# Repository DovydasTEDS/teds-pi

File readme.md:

# teds pi
  
RK3588S based SBC with LPDDR4X RAM in a hopefully pi-shaped shape (what)

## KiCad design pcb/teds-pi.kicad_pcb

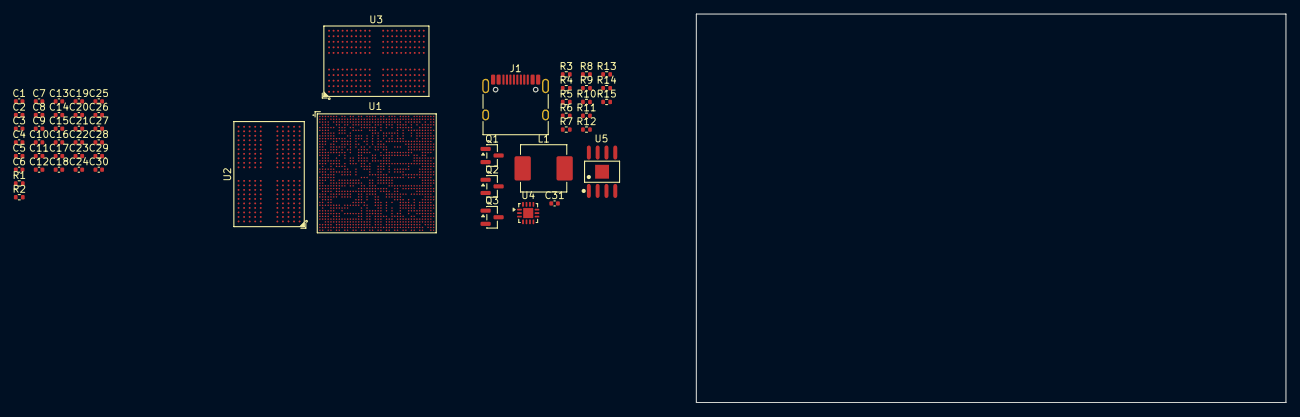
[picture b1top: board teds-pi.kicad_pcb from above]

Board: 6 copper layers, 85.0 x 56.0 mm, 56 parts (0 on the bottom side), 149 nets, no tracks yet.

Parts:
C1, C19: 2.2uF; C_0402_1005Metric
C2, C6, C8, C13, C14, C24, C25, C26, C27, C28, C29, C30, C31: 0.1uF; C_0402_1005Metric
C3, C7, C9, C10, C15, C16, C17, C18: 4.7uF; C_0402_1005Metric
C4, C5, C11, C12, C20, C21, C22, C23: 1uF; C_0402_1005Metric
J1: USB_C_Receptacle_USB2.0_16P; USB_C_Receptacle_HRO_TYPE-C-31-M-12
L1: 4.7uH; L_Changjiang_FXL0630
Q1, Q2: AO3401A; SOT-23
Q3: 2N7002; SOT-23
R1, R2: 240R; R_0402_1005Metric
R3, R4, R5, R6: 49.9R; R_0402_1005Metric
R7, R8: 4k7; R_0402_1005Metric
R9: 10R; R_0402_1005Metric
R10: 10K; R_0402_1005Metric
R11, R13: 100k; R_0402_1005Metric
R12: 10k; R_0402_1005Metric
R14: 44.2k; R_0402_1005Metric
R15: 6.04k; R_0402_1005Metric
U1: BGA-1253_L17.0-W17.0-P0.40-TL
U2, U3: FBGA-200_L15.0-W10.0-BL_K4F6E3S4HM
U4: FUSB302BMPX; WQFN-14-1EP_2.5x2.5mm_P0.5mm_EP1.45x1.45mm
U5: SOIC-8_L5.0-W4.0-P1.27-LS6.0-BL-EP2.0

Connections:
+0V6_DDR: C9.1, C10.1, C11.1, C12.1, C13.1, C14.1, C16.1, C18.1, C21.1, C23.1, C26.1, C28.1, C29.1, C30.1, U1.H14 (DDR_CH1_VDDQ_1), U1.H15 (DDR_CH1_VDDQ_2), U1.H16 (DDR_CH1_VDDQ_3), U1.H18 (DDR_CH1_VDDQ_4), U1.H20 (DDR_CH1_VDDQ_5), U1.K9 (DDR_CH0_VDDQ_CK_1), U1.L9 (DDR_CH0_VDDQ_CK_2), U1.M6 (DDR_CH0_VDDQ_CKE_1), U1.M7 (DDR_CH0_VDDQ_CKE_2), U1.P10 (DDR_CH0_VDDQ_1), U1.R10 (DDR_CH0_VDDQ_2), U1.T10 (DDR_CH0_VDDQ_3), U1.V10 (DDR_CH0_VDDQ_4), U1.W10 (DDR_CH0_VDDQ_5), U1.Y10 (DDR_CH0_VDDQ_6), U2.AA3 (VDDQ), U2.AA5 (VDDQ), U2.AA8 (VDDQ), U2.AA10 (VDDQ), U2.B3 (VDDQ), U2.B5 (VDDQ), U2.B8 (VDDQ), U2.B10 (VDDQ), U2.D1 (VDDQ), U2.D5 (VDDQ), U2.D8 (VDDQ), U2.D12 (VDDQ), U2.F3 (VDDQ), U2.F10 (VDDQ), U2.U3 (VDDQ), U2.U10 (VDDQ), U2.W1 (VDDQ), U2.W5 (VDDQ), U2.W8 (VDDQ), U2.W12 (VDDQ), U3.AA3 (VDDQ), U3.AA5 (VDDQ), U3.AA8 (VDDQ), U3.AA10 (VDDQ), U3.B3 (VDDQ), U3.B5 (VDDQ), U3.B8 (VDDQ), U3.B10 (VDDQ), U3.D1 (VDDQ), U3.D5 (VDDQ), U3.D8 (VDDQ), U3.D12 (VDDQ), U3.F3 (VDDQ), U3.F10 (VDDQ), U3.U3 (VDDQ), U3.U10 (VDDQ), U3.W1 (VDDQ), U3.W5 (VDDQ), U3.W8 (VDDQ), U3.W12 (VDDQ)
+1V1_DDR: C3.1, C4.1, C5.1, C6.1, C7.1, C8.1, C15.1, C17.1, C20.1, C22.1, C25.1, C27.1, U2.A4 (VDD2), U2.A9 (VDD2), U2.AB4 (VDD2), U2.AB9 (VDD2), U2.F5 (VDD2), U2.F8 (VDD2), U2.H1 (VDD2), U2.H5 (VDD2), U2.H8 (VDD2), U2.H12 (VDD2), U2.K1 (VDD2), U2.K3 (VDD2), U2.K10 (VDD2), U2.K12 (VDD2), U2.N1 (VDD2), U2.N3 (VDD2), U2.N10 (VDD2), U2.N12 (VDD2), U2.R1 (VDD2), U2.R5 (VDD2), U2.R8 (VDD2), U2.R12 (VDD2), U2.U5 (VDD2), U2.U8 (VDD2), U3.A4 (VDD2), U3.A9 (VDD2), U3.AB4 (VDD2), U3.AB9 (VDD2), U3.F5 (VDD2), U3.F8 (VDD2), U3.H1 (VDD2), U3.H5 (VDD2), U3.H8 (VDD2), U3.H12 (VDD2), U3.K1 (VDD2), U3.K3 (VDD2), U3.K10 (VDD2), U3.K12 (VDD2), U3.N1 (VDD2), U3.N3 (VDD2), U3.N10 (VDD2), U3.N12 (VDD2), U3.R1 (VDD2), U3.R5 (VDD2), U3.R8 (VDD2), U3.R12 (VDD2), U3.U5 (VDD2), U3.U8 (VDD2)
+1V8_DDR: C19.1, C24.1, U1.L15 (DDR_CH1_PLL_AVDD1V8), U1.Y14 (DDR_CH0_PLL_AVDD1V8), U2.F1 (VDD1), U2.F12 (VDD1), U2.G4 (VDD1), U2.G9 (VDD1), U2.T4 (VDD1), U2.T9 (VDD1), U2.U1 (VDD1), U2.U12 (VDD1), U3.F1 (VDD1), U3.F12 (VDD1), U3.G4 (VDD1), U3.G9 (VDD1), U3.T4 (VDD1), U3.T9 (VDD1), U3.U1 (VDD1), U3.U12 (VDD1)
/CC_INT_L: R10.2, U4.5 (INT_N)
/DDR_CH0_A0_A: U1.U1 (DDR_CH0_A0_A), U2.H2 (CA0_a)
/DDR_CH0_A0_B: U1.U2 (DDR_CH0_A0_B), U2.R2 (CA0_b)
/DDR_CH0_A1_A: U1.AC2 (DDR_CH0_A1_A), U2.J2 (CA1_a)
/DDR_CH0_A1_B: U1.R2 (DDR_CH0_A1_B), U2.P2 (CA1_b)
/DDR_CH0_A2_A: U1.AF1 (DDR_CH0_A2_A), U2.H9 (CA2_a)
/DDR_CH0_A2_B: U1.R1 (DDR_CH0_A2_B), U2.R9 (CA2_b)
/DDR_CH0_A3_A: U1.AL2 (DDR_CH0_A3_A), U2.H10 (CA3_a)
/DDR_CH0_A3_B: U1.D2 (DDR_CH0_A3_B), U2.R10 (CA3_b)
/DDR_CH0_A4_A: U1.Y1 (DDR_CH0_A4_A), U2.H11 (CA4_a)
/DDR_CH0_A4_B: U1.E1 (DDR_CH0_A4_B), U2.R11 (CA4_b)
/DDR_CH0_A5_A: U1.AG2 (DDR_CH0_A5_A), U2.J11 (CA5_a)
/DDR_CH0_A5_B: U1.L1 (DDR_CH0_A5_B), U2.P11 (CA5_b)
/DDR_CH0_CKB_A: U1.AA1 (DDR_CH0_CKB_A), U2.J9 (CK_c_a)
/DDR_CH0_CKB_B: U1.V1 (DDR_CH0_CKB_B), U2.P9 (CK_c_b)
/DDR_CH0_CK_A: U1.AA2 (DDR_CH0_CK_A), U2.J8 (CK_t_a)
/DDR_CH0_CK_B: U1.V2 (DDR_CH0_CK_B), U2.P8 (CK_t_b)
/DDR_CH0_DM0_A: U1.AE1 (DDR_CH0_DM0_A), U2.C3 (DMI0_a)
/DDR_CH0_DM0_B: U1.V5 (DDR_CH0_DM0_B), U2.Y3 (DMI0_b)
/DDR_CH0_DM1_A: U1.AK4 (DDR_CH0_DM1_A), U2.C10 (DMI1_a)
/DDR_CH0_DM1_B: U1.G2 (DDR_CH0_DM1_B), U2.Y10 (DMI1_b)
/DDR_CH0_DQ0_A: U1.AJ2 (DDR_CH0_DQ0_A), U2.B2 (DQ0_a)
/DDR_CH0_DQ0_B: U1.U3 (DDR_CH0_DQ0_B), U2.AA2 (DQ0_b)
/DDR_CH0_DQ1_A: U1.AB4 (DDR_CH0_DQ1_A), U2.C2 (DQ1_a)
/DDR_CH0_DQ1_B: U1.AA5 (DDR_CH0_DQ1_B), U2.Y2 (DQ1_b)
/DDR_CH0_DQ2_A: U1.AJ1 (DDR_CH0_DQ2_A), U2.E2 (DQ2_a)
/DDR_CH0_DQ2_B: U1.N1 (DDR_CH0_DQ2_B), U2.V2 (DQ2_b)
/DDR_CH0_DQ3_A: U1.AB3 (DDR_CH0_DQ3_A), U2.F2 (DQ3_a)
/DDR_CH0_DQ3_B: U1.U5 (DDR_CH0_DQ3_B), U2.U2 (DQ3_b)
/DDR_CH0_DQ4_A: U1.AB5 (DDR_CH0_DQ4_A), U2.F4 (DQ4_a)
/DDR_CH0_DQ4_B: U1.P4 (DDR_CH0_DQ4_B), U2.U4 (DQ4_b)
/DDR_CH0_DQ5_A: U1.AE5 (DDR_CH0_DQ5_A), U2.E4 (DQ5_a)
/DDR_CH0_DQ5_B: U1.P3 (DDR_CH0_DQ5_B), U2.V4 (DQ5_b)
/DDR_CH0_DQ6_A: U1.AE2 (DDR_CH0_DQ6_A), U2.C4 (DQ6_a)
/DDR_CH0_DQ6_B: U1.U4 (DDR_CH0_DQ6_B), U2.Y4 (DQ6_b)
/DDR_CH0_DQ7_A: U1.AF3 (DDR_CH0_DQ7_A), U2.B4 (DQ7_a)
/DDR_CH0_DQ7_B: U1.P5 (DDR_CH0_DQ7_B), U2.AA4 (DQ7_b)
/DDR_CH0_DQ8_A: U1.AK5 (DDR_CH0_DQ8_A), U2.B11 (DQ8_a)
/DDR_CH0_DQ8_B: U1.G5 (DDR_CH0_DQ8_B), U2.AA11 (DQ8_b)
/DDR_CH0_DQ9_A: U1.J3 (DDR_CH0_DQ9_B), U2.C11 (DQ9_a)
/DDR_CH0_DQ9_B: U1.AN5 (DDR_CH0_DQ9_A), U2.Y11 (DQ9_b)
/DDR_CH0_DQ10_A: U1.AN4 (DDR_CH0_DQ10_A), U2.E11 (DQ10_a)
/DDR_CH0_DQ10_B: U1.G4 (DDR_CH0_DQ10_B), U2.V11 (DQ10_b)
/DDR_CH0_DQ11_A: U1.AJ6 (DDR_CH0_DQ11_A), U2.F11 (DQ11_a)
/DDR_CH0_DQ11_B: U1.J4 (DDR_CH0_DQ11_B), U2.U11 (DQ11_b)
/DDR_CH0_DQ12_A: U1.AJ3 (DDR_CH0_DQ12_A), U2.F9 (DQ12_a)
/DDR_CH0_DQ12_B: U1.N5 (DDR_CH0_DQ12_B), U2.U9 (DQ12_b)
/DDR_CH0_DQ13_A: U1.AK3 (DDR_CH0_DQ13_A), U2.E9 (DQ13_a)
/DDR_CH0_DQ13_B: U1.N2 (DDR_CH0_DQ13_B), U2.V9 (DQ13_b)
/DDR_CH0_DQ14_A: U1.AF4 (DDR_CH0_DQ14_A), U2.C9 (DQ14_a)
/DDR_CH0_DQ14_B: U1.J5 (DDR_CH0_DQ14_B), U2.Y9 (DQ14_b)
/DDR_CH0_DQ15_A: U1.AF5 (DDR_CH0_DQ15_A), U2.B9 (DQ15_a)
/DDR_CH0_DQ15_B: U1.N6 (DDR_CH0_DQ15_B), U2.AA9 (DQ15_b)
/DDR_CH0_DQS0N_A: U1.AN1 (DDR_CH0_DQS0P_A), U2.D3 (DQS0_t_a)
/DDR_CH0_DQS0N_B: U1.B2 (DDR_CH0_DQS0P_B), U2.W3 (DQS0_t_b)
/DDR_CH0_DQS0P_A: U1.AN2 (DDR_CH0_DQS0N_A), U2.E3 (DQS0_c_a)
/DDR_CH0_DQS0P_B: U1.B1 (DDR_CH0_DQS0N_B), U2.V3 (DQS0_c_b)
/DDR_CH0_DQS1N_A: U1.AV3 (DDR_CH0_DQS1N_A), U2.D10 (DQS1_t_a)
/DDR_CH0_DQS1N_B: U1.K2 (DDR_CH0_DQS1N_B), U2.W10 (DQS1_t_b)
/DDR_CH0_DQS1P_A: U1.AV4 (DDR_CH0_DQS1P_A), U2.E10 (DQS1_c_a)
/DDR_CH0_DQS1P_B: U1.K1 (DDR_CH0_DQS1P_B), U2.V10 (DQS1_c_b)
/DDR_CH0_LP4/4X_CKE0_A: R3.2, U1.AK1 (DDR_CH0_LP4/4X_CKE0/LP5_CS0_A)
/DDR_CH0_LP4/4X_CKE0_B: R4.2, U1.H2 (DDR_CH0_LP4/4X_CKE0/LP5_CS0_B)
/DDR_CH0_LP4/4X_CS0_A: U1.Y2 (DDR_CH0_LP4/4X_CS0_A), U2.H4 (CS_a)
/DDR_CH0_LP4/4X_CS0_B: U1.J1 (DDR_CH0_LP4/4X_CS0_B), U2.R4 (CS_b)
/DDR_CH0_RESET_A: U1.AG1 (DDR_CH0_RESET_A), U2.T11 (RESET_n)
/DDR_CH1_CKB_C: U1.D21 (DDR_CH1_CKB_C), U3.J9 (CK_c_a)
/DDR_CH1_CKB_D: U1.D23 (DDR_CH1_CKB_D), U3.P9 (CK_c_b)
/DDR_CH1_CK_C: U1.C21 (DDR_CH1_CK_C), U3.J8 (CK_t_a)
/DDR_CH1_CK_D: U1.C23 (DDR_CH1_CK_D), U3.P8 (CK_t_b)
/DDR_CH1_DM0_C: U1.E17 (DDR_CH1_DM0_C), U3.C3 (DMI0_a)
/DDR_CH1_DM0_D: U1.D27 (DDR_CH1_DM0_D), U3.Y3 (DMI0_b)
/DDR_CH1_DM1_C: U1.D13 (DDR_CH1_DM1_C), U3.C10 (DMI1_a)
/DDR_CH1_DM1_D: U1.C33 (DDR_CH1_DM1_D), U3.Y10 (DMI1_b)
/DDR_CH1_DQ0_C: U1.B20 (DDR_CH1_DQ0_C), U3.B2 (DQ0_a)
/DDR_CH1_DQ0_D: U1.A24 (DDR_CH1_DQ0_D), U3.AA2 (DQ0_b)
/DDR_CH1_DQ1_C: U1.E20 (DDR_CH1_DQ1_C), U3.C2 (DQ1_a)
/DDR_CH1_DQ1_D: U1.C25 (DDR_CH1_DQ1_D), U3.Y2 (DQ1_b)
/DDR_CH1_DQ2_C: U1.A20 (DDR_CH1_DQ2_C), U3.E2 (DQ2_a)
/DDR_CH1_DQ2_D: U1.B24 (DDR_CH1_DQ2_D), U3.V2 (DQ2_b)
/DDR_CH1_DQ3_C: U1.F20 (DDR_CH1_DQ3_C), U3.F2 (DQ3_a)
/DDR_CH1_DQ3_D: U1.A28 (DDR_CH1_DQ3_D), U3.U2 (DQ3_b)
/DDR_CH1_DQ4_C: U1.C17 (DDR_CH1_DQ4_C), U3.F4 (DQ4_a)
/DDR_CH1_DQ4_D: U1.D25 (DDR_CH1_DQ4_D), U3.U4 (DQ4_b)
/DDR_CH1_DQ5_C: U1.C16 (DDR_CH1_DQ5_C), U3.E4 (DQ5_a)
/DDR_CH1_DQ5_D: U1.B28 (DDR_CH1_DQ5_D), U3.V4 (DQ5_b)
/DDR_CH1_DQ6_C: U1.D17 (DDR_CH1_DQ6_C), U3.C4 (DQ6_a)
/DDR_CH1_DQ6_D: U1.C27 (DDR_CH1_DQ6_D), U3.Y4 (DQ6_b)
/DDR_CH1_DQ7_C: U1.D16 (DDR_CH1_DQ7_C), U3.B4 (DQ7_a)
/DDR_CH1_DQ7_D: U1.C29 (DDR_CH1_DQ7_D), U3.AA4 (DQ7_b)
/DDR_CH1_DQ8_C: U1.D10 (DDR_CH1_DQ8_C), U3.B11 (DQ8_a)
/DDR_CH1_DQ8_D: U1.D34 (DDR_CH1_DQ8_D), U3.AA11 (DQ8_b)
/DDR_CH1_DQ9_C: U1.D29 (DDR_CH1_DQ9_D), U3.C11 (DQ9_a)
/DDR_CH1_DQ9_D: U1.B12 (DDR_CH1_DQ9_C), U3.Y11 (DQ9_b)
/DDR_CH1_DQ10_C: U1.A12 (DDR_CH1_DQ10_C), U3.E11 (DQ10_a)
/DDR_CH1_DQ10_D: U1.E29 (DDR_CH1_DQ10_D), U3.V11 (DQ10_b)
/DDR_CH1_DQ11_C: U1.C10 (DDR_CH1_DQ11_C), U3.F11 (DQ11_a)
/DDR_CH1_DQ11_D: U1.E32 (DDR_CH1_DQ11_D), U3.U11 (DQ11_b)
/DDR_CH1_DQ12_C: U1.C13 (DDR_CH1_DQ12_C), U3.F9 (DQ12_a)
/DDR_CH1_DQ12_D: U1.B32 (DDR_CH1_DQ12_D), U3.U9 (DQ12_b)
/DDR_CH1_DQ13_C: U1.E13 (DDR_CH1_DQ13_C), U3.E9 (DQ13_a)
/DDR_CH1_DQ13_D: U1.C34 (DDR_CH1_DQ13_D), U3.V9 (DQ13_b)
/DDR_CH1_DQ14_C: U1.A16 (DDR_CH1_DQ14_C), U3.C9 (DQ14_a)
/DDR_CH1_DQ14_D: U1.C32 (DDR_CH1_DQ14_D), U3.Y9 (DQ14_b)
/DDR_CH1_DQ15_C: U1.B16 (DDR_CH1_DQ15_C), U3.B9 (DQ15_a)
/DDR_CH1_DQ15_D: U1.A32 (DDR_CH1_DQ15_D), U3.AA9 (DQ15_b)
/DDR_CH1_DQS0N_C: U1.A9 (DDR_CH1_DQS0P_C), U3.D3 (DQS0_t_a)
/DDR_CH1_DQS0N_D: U1.B41 (DDR_CH1_DQS0P_D), U3.W3 (DQS0_t_b)
/DDR_CH1_DQS0P_C: U1.B9 (DDR_CH1_DQS0N_C), U3.E3 (DQS0_c_a)
/DDR_CH1_DQS0P_D: U1.A41 (DDR_CH1_DQS0N_D), U3.V3 (DQS0_c_b)
/DDR_CH1_DQS1N_C: U1.A4 (DDR_CH1_DQS1N_C), U3.D10 (DQS1_t_a)
/DDR_CH1_DQS1N_D: U1.C36 (DDR_CH1_DQS1N_D), U3.W10 (DQS1_t_b)
/DDR_CH1_DQS1P_C: U1.A3 (DDR_CH1_DQS1P_C), U3.E10 (DQS1_c_a)
/DDR_CH1_DQS1P_D: U1.D36 (DDR_CH1_DQS1P_D), U3.V10 (DQS1_c_b)
/DDR_CH1_LP4/4X_CKE0_C: R5.2, U1.A18 (DDR_CH1_LP4/4X_CKE0/LP5_CS0_C)
/DDR_CH1_LP4/4X_CKE0_D: R6.2, U1.A35 (DDR_CH1_LP4/4X_CKE0/LP5_CS0_D)
/DDR_CH1_LP4/4X_CS0_C: U1.B15 (DDR_CH1_LP4/4X_CS0_C), U3.R4 (CS_b)
/DDR_CH1_LP4/4X_CS0_D: U1.B30 (DDR_CH1_LP4/4X_CS0_D), U3.H4 (CS_a)
/DDR_CH1_RESET_C: U1.B13 (DDR_CH1_RESET_C), U3.T11 (RESET_n)
/I2C6_SCL_M0: R8.2, U1.AG39 (I2S1_SDI3_M1/PDM0_SDI1_M1/I2C6_SCL_M0/U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), U4.6 (SCL)
/I2C6_SDA_M0: R7.2, U1.AL40 (I2S1_SDI2_M1/PDM0_SDI0_M1/I2C6_SDA_M0/U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), U4.7 (SDA)
/VBUS_MCU_EN: Q3.1 (G), R12.1, U1.W41 (PMIC_SLEEP1/GPIO0_A2_d)
/VBUS_TYPEC: J1.A4 (VBUS), J1.A9 (VBUS), J1.B4 (VBUS), J1.B9 (VBUS), Q1.2 (S), R9.1, R11.1
/VCC_3V3_S0: C31.1, R7.1, R8.1, U4.3 (VDD), U4.4 (VDD)
/VCC_SYS: L1.1, R14.2
/VCC_SYS_IN: Q2.2 (S), R13.1, U5.7 (VIN), U5.8 (VIN)
GND: C1.2, C2.2, C3.2, C4.2, C5.2, C6.2, C7.2, C8.2, C9.2, C10.2, C11.2, C12.2, C13.2, C14.2, C15.2, C16.2, C17.2, C18.2, C19.2, C20.2, C21.2, C22.2, C23.2, C24.2, C25.2, C26.2, C27.2, C28.2, C29.2, C30.2, C31.2, J1.A1 (GND), J1.A12 (GND), J1.B1 (GND), J1.B12 (GND), J1.SH (SHIELD), Q3.2 (S), R1.2, R2.2, R12.2, R15.2, U1.AA14 (DDR_CH0_PLL_AVSS), U1.N15 (DDR_CH1_PLL_AVSS), U2.A3 (VSS), U2.A10 (VSS), U2.AB3 (VSS), U2.AB5 (VSS), U2.AB8 (VSS), U2.AB10 (VSS), U2.C1 (VSS), U2.C5 (VSS), U2.C8 (VSS), U2.C12 (VSS), U2.D2 (VSS), U2.D4 (VSS), U2.D9 (VSS), U2.D11 (VSS), U2.E1 (VSS), U2.E5 (VSS), U2.E8 (VSS), U2.E12 (VSS), U2.G1 (VSS), U2.G2 (ODT_CA_a), U2.G3 (VSS), U2.G5 (VSS), U2.G8 (VSS), U2.G10 (VSS), U2.G12 (VSS), U2.J1 (VSS), U2.J3 (VSS), U2.J10 (VSS), U2.J12 (VSS), U2.K2 (VSS), U2.K4 (VSS), U2.K9 (VSS), U2.K11 (VSS), U2.N2 (VSS), U2.N4 (VSS), U2.N9 (VSS), U2.N11 (VSS), U2.P1 (VSS), U2.P3 (VSS), U2.P10 (VSS), U2.P12 (VSS), U2.T1 (VSS), U2.T2 (ODT_CA_b), U2.T3 (VSS), U2.T5 (VSS), U2.T8 (VSS), U2.T10 (VSS), U2.T12 (VSS), U2.V1 (VSS), U2.V5 (VSS), U2.V8 (VSS), U2.V12 (VSS), U2.W2 (VSS), U2.W4 (VSS), U2.W9 (VSS), U2.W11 (VSS), U2.Y1 (VSS), U2.Y5 (VSS), U2.Y8 (VSS), U2.Y12 (VSS), U3.A3 (VSS), U3.A10 (VSS), U3.AB3 (VSS), U3.AB5 (VSS), U3.AB8 (VSS), U3.AB10 (VSS), U3.C1 (VSS), U3.C5 (VSS), U3.C8 (VSS), U3.C12 (VSS), U3.D2 (VSS), U3.D4 (VSS), U3.D9 (VSS), U3.D11 (VSS), U3.E1 (VSS), U3.E5 (VSS), U3.E8 (VSS), U3.E12 (VSS), U3.G1 (VSS), U3.G2 (ODT_CA_a), U3.G3 (VSS), U3.G5 (VSS), U3.G8 (VSS), U3.G10 (VSS), U3.G12 (VSS), U3.J1 (VSS), U3.J3 (VSS), U3.J10 (VSS), U3.J12 (VSS), U3.K2 (VSS), U3.K4 (VSS), U3.K9 (VSS), U3.K11 (VSS), U3.N2 (VSS), U3.N4 (VSS), U3.N9 (VSS), U3.N11 (VSS), U3.P1 (VSS), U3.P3 (VSS), U3.P10 (VSS), U3.P12 (VSS), U3.T1 (VSS), U3.T2 (ODT_CA_b), U3.T3 (VSS), U3.T5 (VSS), U3.T8 (VSS), U3.T10 (VSS), U3.T12 (VSS), U3.V1 (VSS), U3.V5 (VSS), U3.V8 (VSS), U3.V12 (VSS), U3.W2 (VSS), U3.W4 (VSS), U3.W9 (VSS), U3.W11 (VSS), U3.Y1 (VSS), U3.Y5 (VSS), U3.Y8 (VSS), U3.Y12 (VSS), U4.8 (GND), U4.9 (GND), U4.12 (VCONN), U4.13 (VCONN), U4.15 (GND), U5.9 (GND)
unnamed: J1.A5 (CC1), U4.10 (CC1), U4.11 (CC1)
unnamed: J1.B5 (CC2), U4.1 (CC2), U4.14 (CC2)
unnamed: J1.A6 (D+), J1.B6 (D+)
unnamed: J1.A7 (D-), J1.B7 (D-)
unnamed: Q1.3 (D), Q2.3 (D)
unnamed: Q1.1 (G), Q2.1 (G), Q3.3 (D), R11.2
unnamed: U1.T12 (DDR_CH0_VDD_1), U1.T13 (DDR_CH0_VDD_2), U1.U12 (DDR_CH0_VDD_3), U1.U13 (DDR_CH0_VDD_4), U1.V12 (DDR_CH0_VDD_MIF_1), U1.V13 (DDR_CH0_VDD_MIF_2), U1.V14 (DDR_CH0_VDD_MIF_3)
unnamed: U1.J18 (DDR_CH1_VDD_1), U1.J20 (DDR_CH1_VDD_MIF_1), U1.K18 (DDR_CH1_VDD_2), U1.K20 (DDR_CH1_VDD_MIF_2), U1.L18 (DDR_CH1_VDD_3), U1.L20 (DDR_CH1_VDD_MIF_3)
unnamed: R3.1, U2.J4 (CKE_a)
unnamed: R4.1, U2.P4 (CKE_b)
unnamed: R1.1, U2.A5 (ZQ)
unnamed: R5.1, U3.J4 (CKE_a)
unnamed: R6.1, U3.P4 (CKE_b)
unnamed: R2.1, U3.A5 (ZQ)
unnamed: R9.2, U4.2 (VBUS)
unnamed: R13.2, U5.3 (EN)
unnamed: R14.1, R15.1, U5.5 (FB)
unnamed: L1.2, U5.2 (LX), U5.6 (VCC)
VCC_1V8_S3: C1.1, C2.1, R10.1

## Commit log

2026-06-08 add gitignore
2026-06-08 add libs
2026-06-08 inital PCB - connect ram
2026-06-08 add POWAH! sorta.. for now...
2026-06-08 add readme for funsies :)
2026-06-11 add rk806 + more POWAH!
